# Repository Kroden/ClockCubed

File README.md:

ClockCubed
==========

PDI Capstone project turned open source hardware

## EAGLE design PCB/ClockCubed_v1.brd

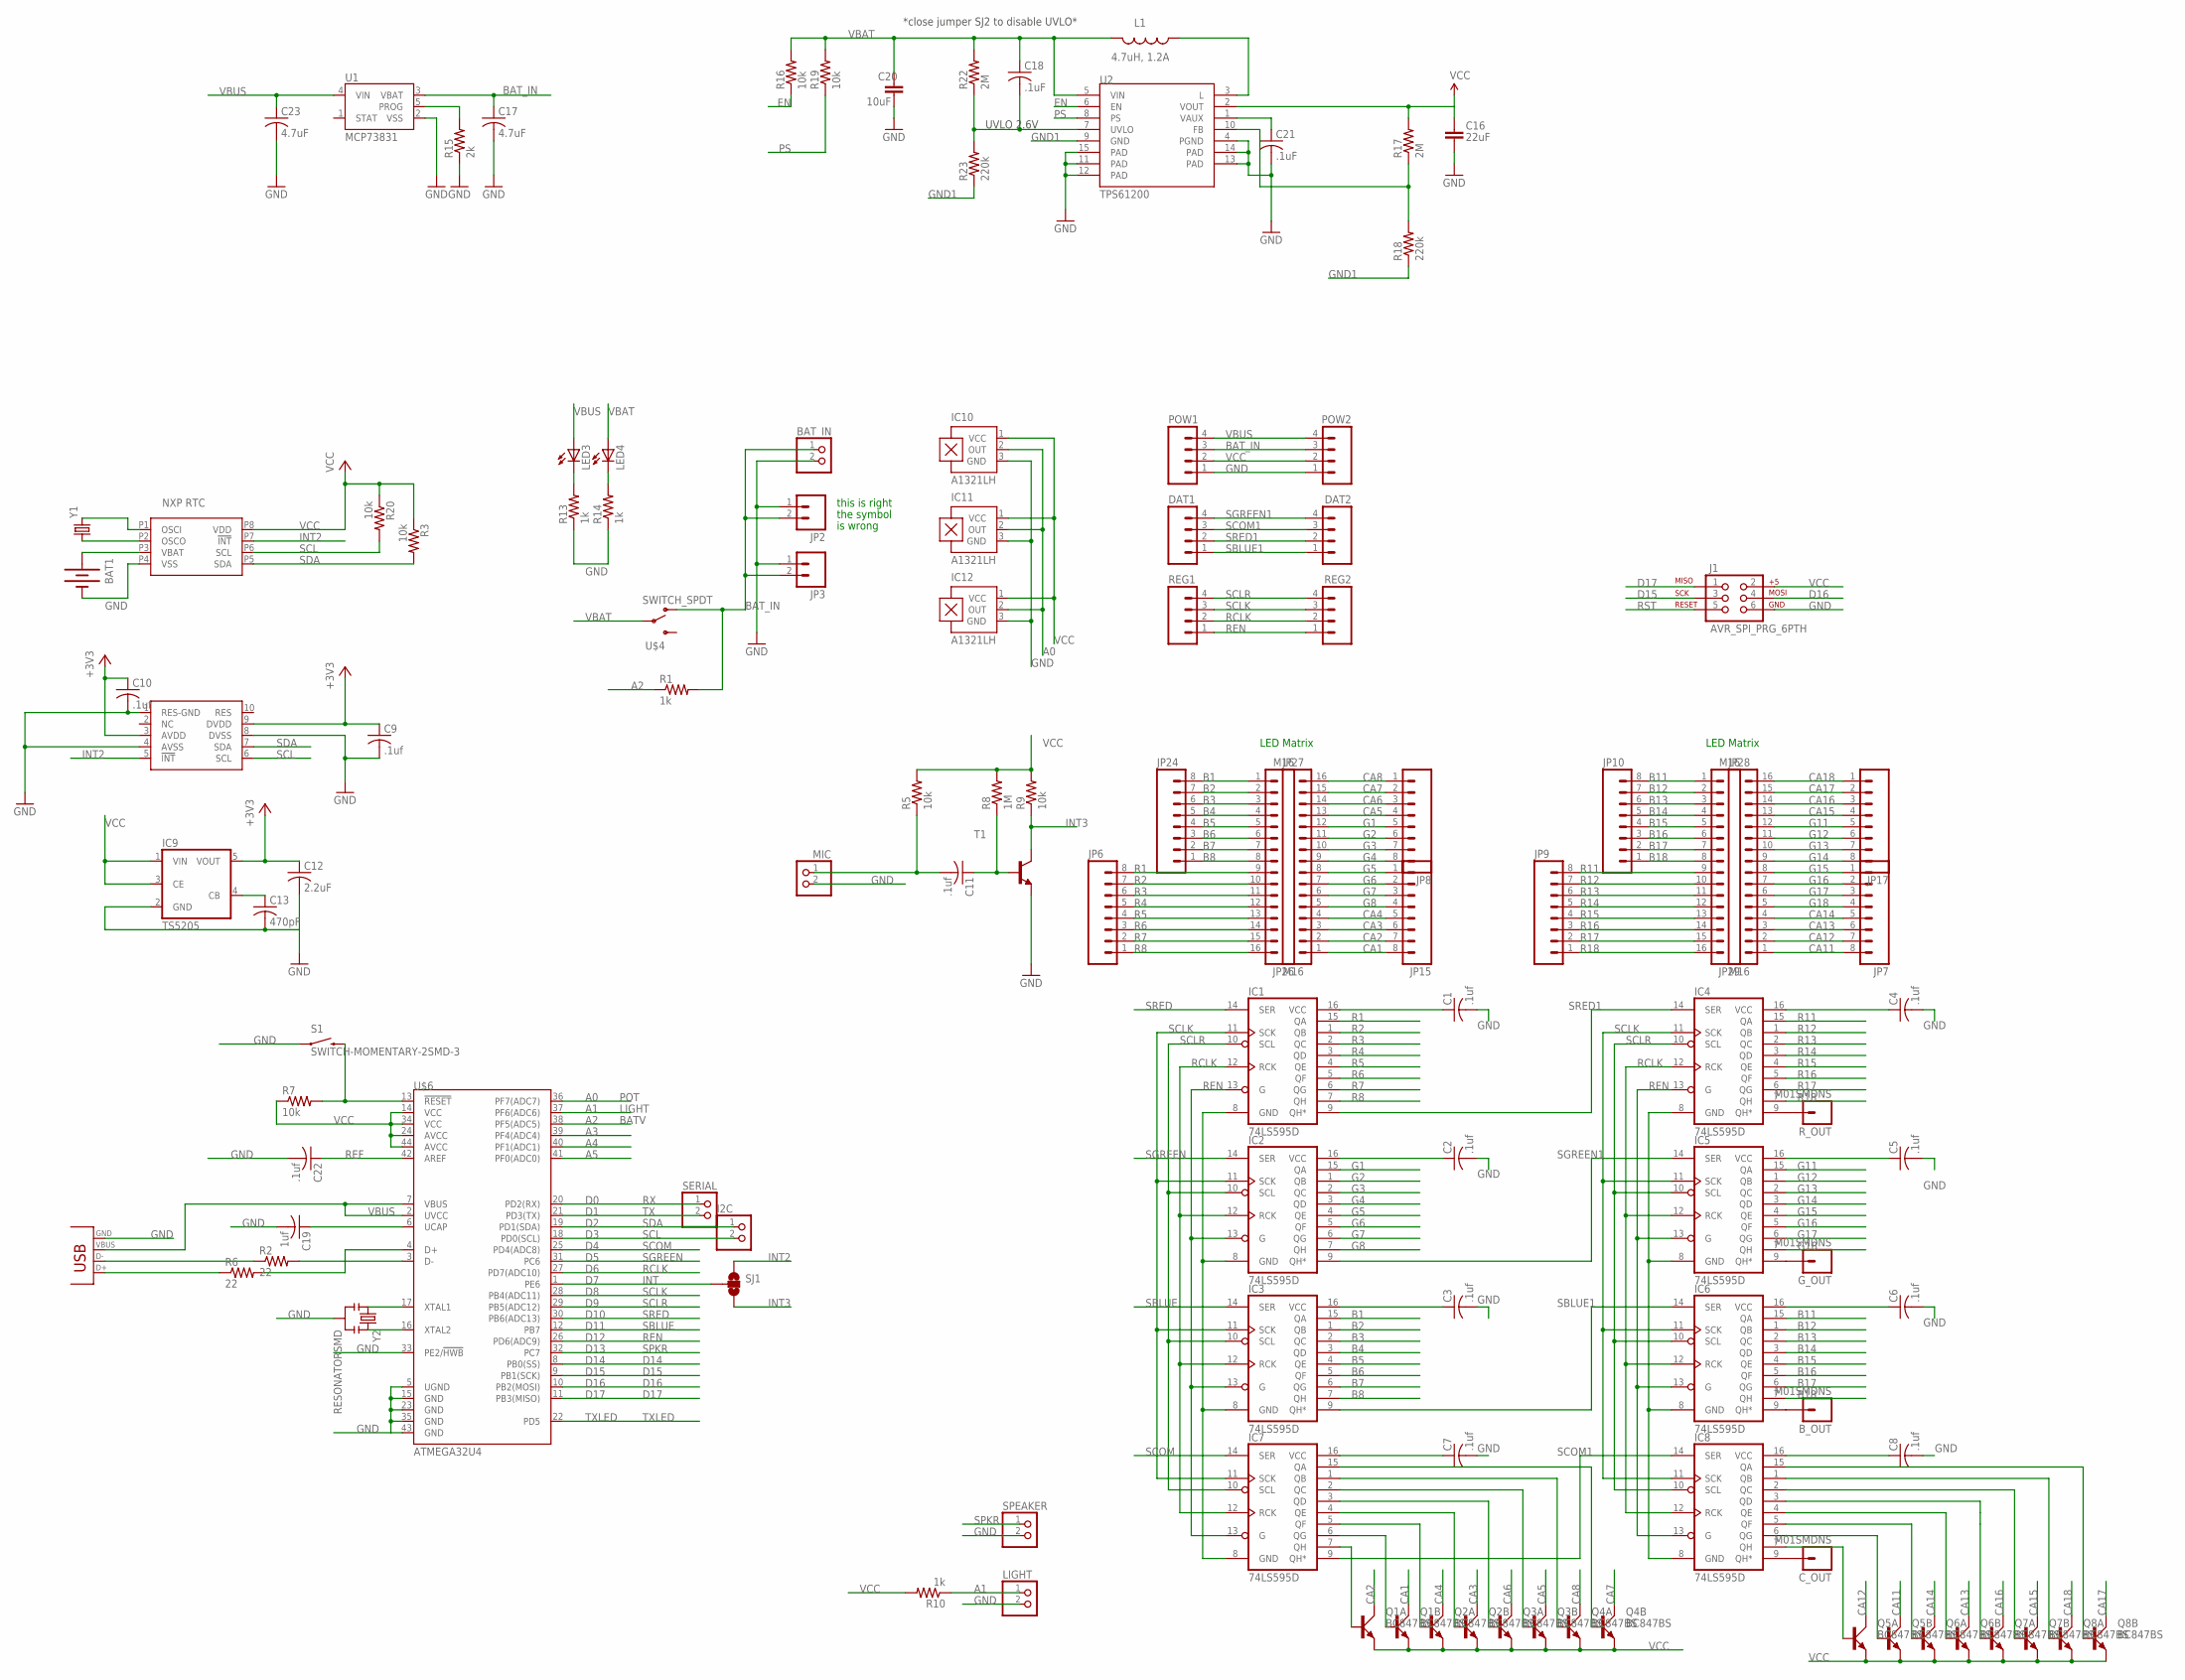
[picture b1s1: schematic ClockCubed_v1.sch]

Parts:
BAT1: BATTERY12MM; BATTCON_12MM
BAT_IN: PINHD-1X2; 1X02
B_OUT: M01SMDNS; 1X01NS
C1, C2, C3, C4, C5, C6, C7, C8, C9, C10, C11, C22: .1uf; C0603
C12: 2.2uF; C0603
C13: 470pF; C0603
C16: 22uF; 0805
C17, C23: 4.7uF; C0603
C18, C21: .1uF; C0603
C19: 1uf; C0603
C20: 10uF; 1206
C_OUT: M01SMDNS; 1X01NS
DAT1, DAT2: M04PTH; 1X04
G_OUT: M01SMDNS; 1X01NS
I2C: PINHD-1X2; 1X02
IC1, IC2, IC3, IC4, IC5, IC6, IC7, IC8: 74LS595D; SO16
IC9: TS5205; SOT25
IC10, IC11, IC12: A1321LH; SOT23-W
J1: AVR_SPI_PRG_6PTH; 2X3
JP2, JP3: M02JST-PTH-2; JST-2-PTH
JP6, JP7, JP8, JP9, JP10, JP15, JP17, JP24: M08SMD-COMBO; 1X08_SMD_COMBINED
JP26, JP27, JP28, JP29: M16; 1X16_NS
L1: 4.7uH, 1.2A; CDRH2D09
LED3, LED4: LEDCHIPLED_0805; CHIPLED_0805
LIGHT: PINHD-1X2; 1X02
MIC: PINHD-1X2; 1X02
POW1, POW2: M04PTH; 1X04
Q1, Q2, Q3, Q4, Q5, Q6, Q7, Q8: BC847BS; SOT363_PHILIPS
R1, R10, R13, R14: 1k; 0603-RES
R2, R6: 22; 0603-RES
R3, R5, R7, R9, R16, R19, R20: 10k; 0603-RES
R8: 1M; 0603-RES
R15: 2k; 0603-RES
R17, R22: 2M; 0603-RES
R18, R23: 220k; 0603-RES
REG1, REG2: M04PTH; 1X04
R_OUT: M01SMDNS; 1X01NS
S1: SWITCH-MOMENTARY-2SMD-3; TACTILE_SWITCH_SMD-3
SERIAL: PINHD-1X2; 1X02
SJ1: SOLDERJUMPER_2WAYS; SJ_3
SPEAKER: PINHD-1X2; 1X02
T1: -NPN-SOT23-EBC; SOT23-EBC
U1: MCP73831; SOT23-5
U2: TPS61200; QFN-10_PAD
U$1: USB_MICROB; USB-MICROB
U$2: MMA7660FC; DFN-10
U$3: NXP-RTC; HVSON8
U$4: SWITCH_SPDT; KPS-1290
U$6: ATMEGA32U4; TQFP44
Y1: CRYSTAL5X2; CRYSTAL-SMD-5X2
Y2: RESONATORSMD; RESONATOR-SMD

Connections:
+3V3: C9.1, C10.1, C12.1, IC9.5 (VOUT), U$2.3 (AVDD), U$2.9 (DVDD)
A0: IC10.2 (OUT), IC11.2 (OUT), IC12.2 (OUT), U$6.36 (PF7(ADC7))
A1: LIGHT.1, R10.1, U$6.37 (PF6(ADC6))
A2: R1.1, U$6.38 (PF5(ADC5))
A3: U$6.39 (PF4(ADC4))
A4: U$6.40 (PF1(ADC1))
A5: U$6.41 (PF0(ADC0))
B1: IC3.15 (QA), JP24.8, JP26.1
B2: IC3.1 (QB), JP24.7, JP26.2
B3: IC3.2 (QC), JP24.6, JP26.3
B4: IC3.3 (QD), JP24.5, JP26.4
B5: IC3.4 (QE), JP24.4, JP26.5
B6: IC3.5 (QF), JP24.3, JP26.6
B7: IC3.6 (QG), JP24.2, JP26.7
B8: IC3.7 (QH), JP24.1, JP26.8
B11: IC6.15 (QA), JP10.8, JP29.1
B12: IC6.1 (QB), JP10.7, JP29.2
B13: IC6.2 (QC), JP10.6, JP29.3
B14: IC6.3 (QD), JP10.5, JP29.4
B15: IC6.4 (QE), JP10.4, JP29.5
B16: IC6.5 (QF), JP10.3, JP29.6
B17: IC6.6 (QG), JP10.2, JP29.7
B18: IC6.7 (QH), JP10.1, JP29.8
BAT_IN: BAT_IN.1, C17.1, JP2.2, JP3.2, POW1.3, POW2.3, R1.2, U1.3 (VBAT), U$4.O
CA1: JP15.8, JP27.1, Q1.3 (C)
CA2: JP15.7, JP27.2, Q1.6 (C)
CA3: JP15.6, JP27.3, Q2.3 (C)
CA4: JP15.5, JP27.4, Q2.6 (C)
CA5: JP8.4, JP27.13, Q3.3 (C)
CA6: JP8.3, JP27.14, Q3.6 (C)
CA7: JP8.2, JP27.15, Q4.3 (C)
CA8: JP8.1, JP27.16, Q4.6 (C)
CA11: JP7.8, JP28.1, Q5.3 (C)
CA12: JP7.7, JP28.2, Q5.6 (C)
CA13: JP7.6, JP28.3, Q6.3 (C)
CA14: JP7.5, JP28.4, Q6.6 (C)
CA15: JP17.4, JP28.13, Q7.3 (C)
CA16: JP17.3, JP28.14, Q7.6 (C)
CA17: JP17.2, JP28.15, Q8.3 (C)
CA18: JP17.1, JP28.16, Q8.6 (C)
D14: U$6.8 (PB0(SS))
D15: J1.3, U$6.9 (PB1(SCK))
D16: J1.4, U$6.10 (PB2(MOSI))
D17: J1.1, U$6.11 (PB3(MISO))
D+: R6.1, U$1.P3
D-: R2.1, U$1.P2
EN: R16.1, U2.6 (EN)
FB: R17.1, R18.2, U2.10 (FB)
G1: IC2.15 (QA), JP8.5, JP27.12
G2: IC2.1 (QB), JP8.6, JP27.11
G3: IC2.2 (QC), JP8.7, JP27.10
G4: IC2.3 (QD), JP8.8, JP27.9
G5: IC2.4 (QE), JP15.1, JP27.8
G6: IC2.5 (QF), JP15.2, JP27.7
G7: IC2.6 (QG), JP15.3, JP27.6
G8: IC2.7 (QH), JP15.4, JP27.5
G11: IC5.15 (QA), JP17.5, JP28.12
G12: IC5.1 (QB), JP17.6, JP28.11
G13: IC5.2 (QC), JP17.7, JP28.10
G14: IC5.3 (QD), JP17.8, JP28.9
G15: IC5.4 (QE), JP7.1, JP28.8
G16: IC5.5 (QF), JP7.2, JP28.7
G17: IC5.6 (QG), JP7.3, JP28.6
G18: IC5.7 (QH), JP7.4, JP28.5
GND: BAT1.GND (-), BAT_IN.2, C1.2, C2.2, C3.2, C4.2, C5.2, C6.2, C7.2, C8.2, C9.2, C10.2, C12.2, C13.2, C16.2, C17.2, C19.2, C20.2, C21.2, C22.2, C23.2, IC1.8 (GND), IC2.8 (GND), IC3.8 (GND), IC4.8 (GND), IC5.8 (GND), IC6.8 (GND), IC7.8 (GND), IC8.8 (GND), IC9.2 (GND), IC10.3 (GND), IC11.3 (GND), IC12.3 (GND), J1.6, JP2.1, JP3.1, LIGHT.2, MIC.2, POW1.1, POW2.1, R13.1, R14.1, R15.1, S1.P$1 (1), SPEAKER.2, T1.E, U1.2 (VSS), U2.4 (PGND), U2.11 (PAD), U2.12 (PAD), U2.13 (PAD), U2.14 (PAD), U2.15 (PAD), U$1.P4, U$1.P5, U$1.P$1, U$1.P$2, U$1.P$3, U$1.P$4, U$1.P$5, U$1.P$6, U$2.1 (RES-GND), U$2.4 (AVSS), U$2.8 (DVSS), U$3.P4 (VSS), U$6.5 (UGND), U$6.15 (GND), U$6.23 (GND), U$6.33 (PE2/!HWB), U$6.35 (GND), U$6.43 (GND), Y2.2
GND1: R18.1, R23.1, U2.9 (GND)
INT: SJ1.2, U$6.1 (PE6)
INT2: SJ1.1, U$2.5 (!INT), U$3.P7 (!INT)
INT3: R9.1, SJ1.3, T1.C
unnamed: IC7.7 (QH), Q1.2 (B)
unnamed: IC7.6 (QG), Q1.5 (B)
unnamed: U$6.16 (XTAL2), Y2.3
unnamed: C13.1, IC9.4 (CB)
unnamed: C11.2, MIC.1, R5.1
unnamed: IC8.7 (QH), Q5.2 (B)
unnamed: IC7.5 (QF), Q2.2 (B)
unnamed: IC7.4 (QE), Q2.5 (B)
unnamed: IC7.3 (QD), Q3.2 (B)
unnamed: IC8.6 (QG), Q5.5 (B)
unnamed: R15.2, U1.5 (PROG)
unnamed: IC7.2 (QC), Q3.5 (B)
unnamed: C11.1, R8.1, T1.B
unnamed: IC7.1 (QB), Q4.2 (B)
unnamed: C_OUT.1, IC8.9 (QH*)
unnamed: IC7.15 (QA), Q4.5 (B)
unnamed: U$3.P1 (OSCI), Y1.2
unnamed: U$6.17 (XTAL1), Y2.1
unnamed: U$3.P2 (OSCO), Y1.1
unnamed: BAT1.PWR@1 (+), U$3.P3 (VBAT)
unnamed: IC8.5 (QF), Q6.2 (B)
unnamed: R6.2, U$6.4 (D+)
unnamed: R2.2, U$6.3 (D-)
unnamed: C19.1, U$6.6 (UCAP)
unnamed: B_OUT.1, IC6.9 (QH*)
unnamed: IC8.4 (QE), Q6.5 (B)
unnamed: IC8.3 (QD), Q7.2 (B)
unnamed: IC8.2 (QC), Q7.5 (B)
unnamed: IC8.1 (QB), Q8.2 (B)
unnamed: IC8.15 (QA), Q8.5 (B)
unnamed: LED3.C, R13.2
unnamed: LED4.C, R14.2
unnamed: L1.P$1 (1), U2.3 (L)
unnamed: C21.1, U2.1 (VAUX)
unnamed: G_OUT.1, IC5.9 (QH*)
unnamed: IC4.9 (QH*), R_OUT.1
PS: R19.1, U2.8 (PS)
R1: IC1.15 (QA), JP6.8, JP26.9
R2: IC1.1 (QB), JP6.7, JP26.10
R3: IC1.2 (QC), JP6.6, JP26.11
R4: IC1.3 (QD), JP6.5, JP26.12
R5: IC1.4 (QE), JP6.4, JP26.13
R6: IC1.5 (QF), JP6.3, JP26.14
R7: IC1.6 (QG), JP6.2, JP26.15
R8: IC1.7 (QH), JP6.1, JP26.16
R11: IC4.15 (QA), JP9.8, JP29.9
R12: IC4.1 (QB), JP9.7, JP29.10
R13: IC4.2 (QC), JP9.6, JP29.11
R14: IC4.3 (QD), JP9.5, JP29.12
R15: IC4.4 (QE), JP9.4, JP29.13
R16: IC4.5 (QF), JP9.3, JP29.14
R17: IC4.6 (QG), JP9.2, JP29.15
R18: IC4.7 (QH), JP9.1, JP29.16
RCLK: IC1.12 (RCK), IC2.12 (RCK), IC3.12 (RCK), IC4.12 (RCK), IC5.12 (RCK), IC6.12 (RCK), IC7.12 (RCK), IC8.12 (RCK), REG1.2, REG2.2, U$6.27 (PD7(ADC10))
REF: C22.1, U$6.42 (AREF)
REN: IC1.13 (G), IC2.13 (G), IC3.13 (G), IC4.13 (G), IC5.13 (G), IC6.13 (G), IC7.13 (G), IC8.13 (G), REG1.1, REG2.1, U$6.26 (PD6(ADC9))
RST: J1.5, R7.2, S1.P$2 (2), U$6.13 (!RESET)
RX: SERIAL.1, U$6.20 (PD2(RX))
SBLUE: IC3.14 (SER), U$6.12 (PB7)
SBLUE1: DAT1.1, DAT2.1, IC3.9 (QH*), IC6.14 (SER)
SCL: I2C.2, R20.2, U$2.6 (SCL), U$3.P6 (SCL), U$6.18 (PD0(SCL))
SCLK: IC1.11 (SCK), IC2.11 (SCK), IC3.11 (SCK), IC4.11 (SCK), IC5.11 (SCK), IC6.11 (SCK), IC7.11 (SCK), IC8.11 (SCK), REG1.3, REG2.3, U$6.28 (PB4(ADC11))
SCLR: IC1.10 (SCL), IC2.10 (SCL), IC3.10 (SCL), IC4.10 (SCL), IC5.10 (SCL), IC6.10 (SCL), IC7.10 (SCL), IC8.10 (SCL), REG1.4, REG2.4, U$6.29 (PB5(ADC12))
SCOM: IC7.14 (SER), U$6.25 (PD4(ADC8))
SCOM1: DAT1.3, DAT2.3, IC7.9 (QH*), IC8.14 (SER)
SDA: I2C.1, R3.2, U$2.7 (SDA), U$3.P5 (SDA), U$6.19 (PD1(SDA))
SGREEN: IC2.14 (SER), U$6.31 (PC6)
SGREEN1: DAT1.4, DAT2.4, IC2.9 (QH*), IC5.14 (SER)
SPKR: SPEAKER.1, U$6.32 (PC7)
SRED: IC1.14 (SER), U$6.30 (PB6(ADC13))
SRED1: DAT1.2, DAT2.2, IC1.9 (QH*), IC4.14 (SER)
TX: SERIAL.2, U$6.21 (PD3(TX))
TXLED: U$6.22 (PD5)
UVLO: C18.2, R22.1, R23.2, U2.7 (UVLO)
VBAT: C18.1, C20.1, L1.P$2 (2), LED4.A, R16.2, R19.2, R22.2, U2.5 (VIN), U$4.P
VBUS: C23.1, LED3.A, POW1.4, POW2.4, U1.4 (VIN), U$1.P1, U$6.2 (UVCC), U$6.7 (VBUS)
VCC: C1.1, C2.1, C3.1, C4.1, C5.1, C6.1, C7.1, C8.1, C16.1, IC1.16 (VCC), IC2.16 (VCC), IC3.16 (VCC), IC4.16 (VCC), IC5.16 (VCC), IC6.16 (VCC), IC7.16 (VCC), IC8.16 (VCC), IC9.1 (VIN), IC9.3 (CE), IC10.1 (VCC), IC11.1 (VCC), IC12.1 (VCC), J1.2, POW1.2, POW2.2, Q1.1 (E), Q1.4 (E), Q2.1 (E), Q2.4 (E), Q3.1 (E), Q3.4 (E), Q4.1 (E), Q4.4 (E), Q5.1 (E), Q5.4 (E), Q6.1 (E), Q6.4 (E), Q7.1 (E), Q7.4 (E), Q8.1 (E), Q8.4 (E), R3.1, R5.2, R7.1, R8.2, R9.2, R10.2, R17.2, R20.1, U2.2 (VOUT), U$3.P8 (VDD), U$6.14 (VCC), U$6.24 (AVCC), U$6.34 (VCC), U$6.44 (AVCC)

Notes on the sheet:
TXLED
LED Matrix
POT
LIGHT
BATV
D14
D15
D16
D17
D10
D11
D12
D13
this is right
the symbol
is wrong
UVLO 2.6V
*close jumper SJ2 to disable UVLO*

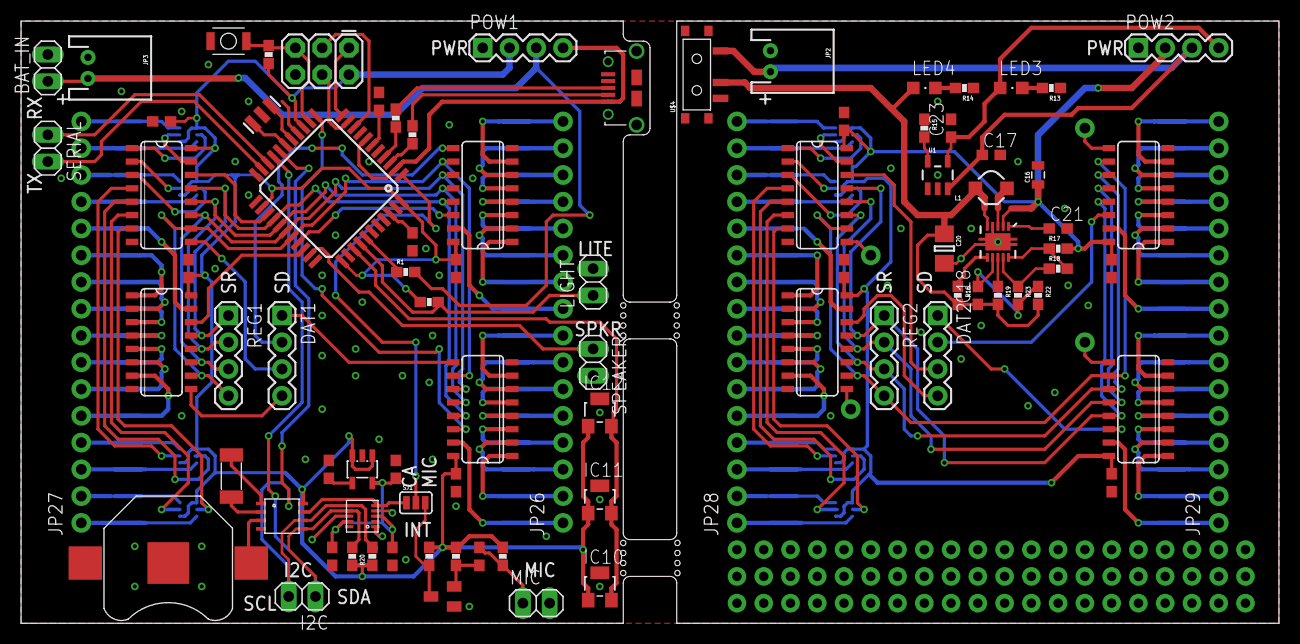
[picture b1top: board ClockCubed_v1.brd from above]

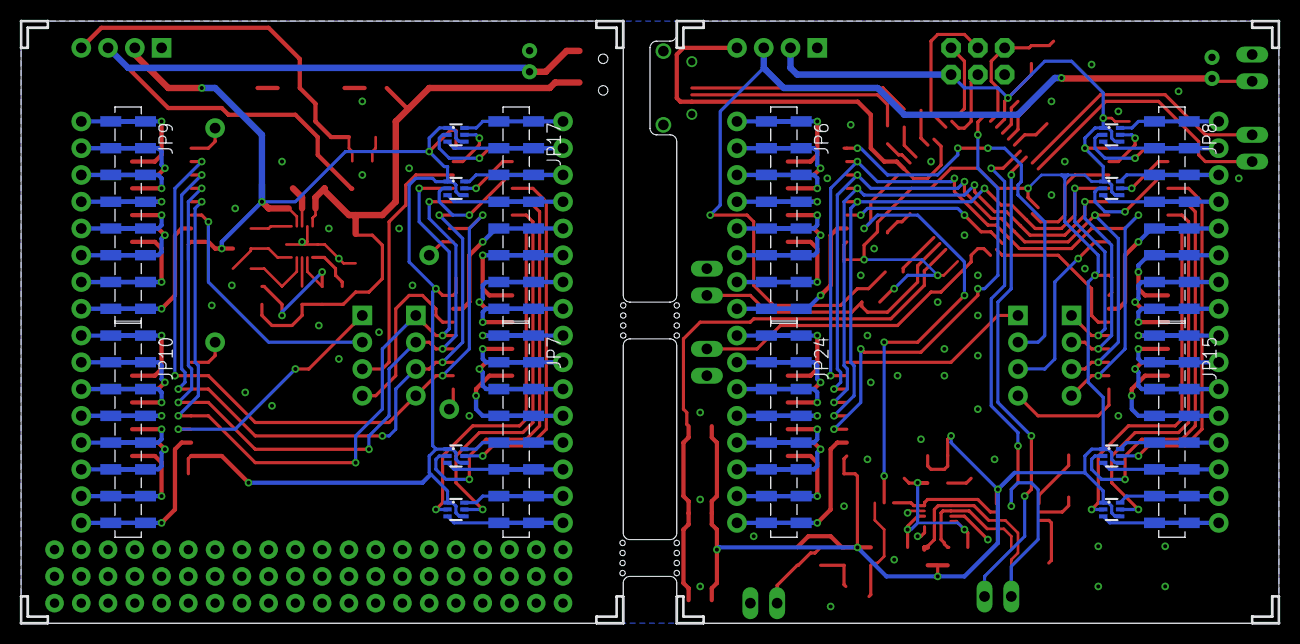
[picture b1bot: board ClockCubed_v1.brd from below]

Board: 2 copper layers, 119.4 x 57.1 mm, 107 parts (16 on the bottom side), 141 nets.

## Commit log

2014-05-17 Initial release
    added pcb and arduino code for initial release
2014-05-17 updated license, added pdf files of board and sch
    updated names in license, created pdf files of schematic and layout
    files, added copyright to schematic
2014-05-17 block diagram
    created block diagram
2014-05-17 font and generator
    added letters to fonts, included font generator excel spreadsheet
2014-05-17 font and generator
    comment concatenation, added 4x8_bot letters to font.h
2014-05-17 as filmed may 17th 2014
    changed some frames to show the functionality, wakeup on alarm, text
    display

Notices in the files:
parts and their libraries:
SparkFun-Connectors: Licensing: CC v3.0 Share-Alike You are welcome to use this library for commercial purposes.
